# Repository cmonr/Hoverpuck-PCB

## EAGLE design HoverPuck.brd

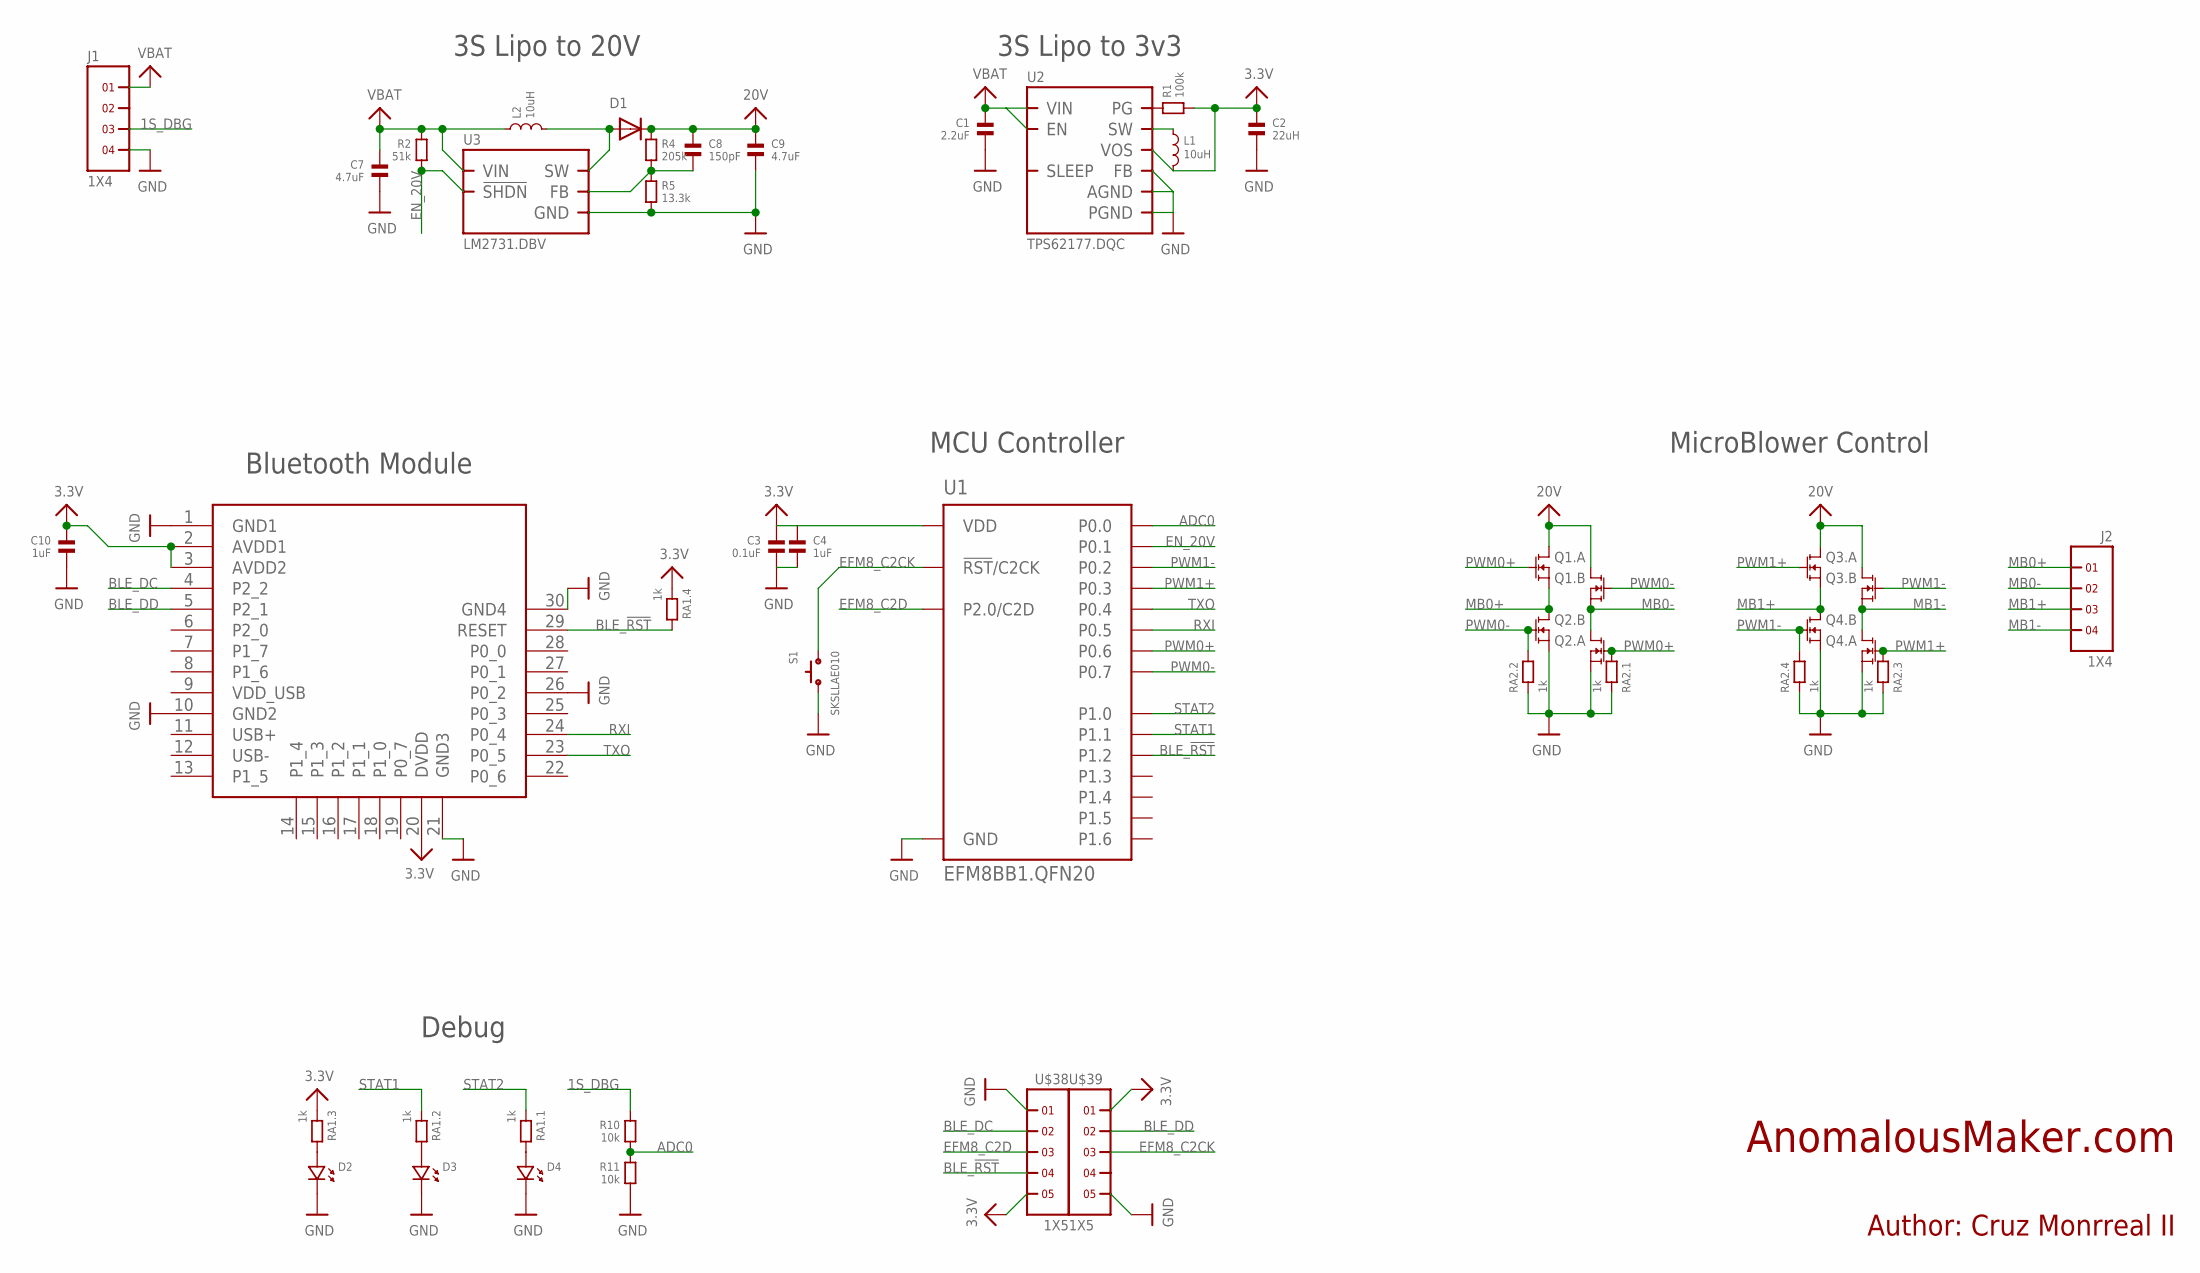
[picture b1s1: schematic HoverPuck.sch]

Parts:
C1: 2.2uF; 0603
C2: 22uH; 0805
C3: 0.1uF; 0603
C4, C10: 1uF; 0603
C7, C9: 4.7uF; 0805
C8: 150pF; 0603
D1: MBR0530T1G; SOD-123
D2, D3, D4: LED.0603; 0603.LED
J1, J2: 1X4
L1: 10uH; LPS4018
L2: 10uH; SRN6045
Q1, Q2, Q3, Q4: FDMA; MICROFET.2X2
R1: 100k; 0603
R2: 51k; 0603
R4: 205k; 0603
R5: 13.3k; 0603
R10, R11: 10k; 0603
RA1, RA2: 1k; 0603.4.C
S1: SKSLLAE010
U1: EFM8BB1.QFN20; QFN20
U2: TPS62177.DQC; DQC
U3: LM2731.DBV; DBV.5
U4: BLE112-A
U$38, U$39: 1X5

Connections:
1S_DBG: J1.3, R10.1
3.3V: C2.1, C3.1, C4.1, C10.1, L1.2, R1.2, RA1.5 (1), RA1.7 (1), U1.4 (VDD), U2.10 (VOS), U4.2 (AVDD1), U4.3 (AVDD2), U4.20 (DVDD), U$38.5, U$39.1
20V: C8.1, C9.1, D1.C, Q1.3 (D), Q1.6 (D), Q1.PAD@1 (D), Q1.PAD@2 (D), Q3.3 (D), Q3.6 (D), Q3.PAD@1 (D), Q3.PAD@2 (D), R4.1
ADC0: R10.2, R11.1, U1.2 (P0.0)
BLE_!RST: RA1.8 (2), U1.11 (P1.2), U4.29 (RESET), U$38.4
BLE_DC: U4.4 (P2_2), U$38.2
BLE_DD: U4.5 (P2_1), U$39.2
EFM8_C2CK: S1.1, U1.5 (!RST!/C2CK), U$39.3
EFM8_C2D: U1.6 (P2.0/C2D), U$38.3
EN_20V: R2.2, U1.1 (P0.1), U3.4 (!SHDN)
GND: C1.2, C2.2, C3.2, C4.2, C7.2, C9.2, C10.2, D2.P$2 (2), D3.P$2 (2), D4.P$2 (2), J1.4, Q2.1 (S), Q2.4 (S), Q4.1 (S), Q4.4 (S), R5.2, R11.2, RA2.1, RA2.3 (1), RA2.5 (1), RA2.7 (1), S1.2, U1.3 (GND), U1.12 (GND), U1.PAD (GND), U2.1 (PGND), U2.5 (FB), U2.6 (AGND), U2.PAD (PGND), U3.2 (GND), U4.1 (GND1), U4.10 (GND2), U4.21 (GND3), U4.26 (P0_2), U4.30 (GND4), U$38.1, U$39.5
MB0+: J2.1, Q1.1 (S), Q2.3 (D), Q2.PAD@2 (D)
MB0-: J2.2, Q1.4 (S), Q2.6 (D), Q2.PAD@1 (D)
MB1+: J2.3, Q3.1 (S), Q4.3 (D), Q4.PAD@2 (D)
MB1-: J2.4, Q3.4 (S), Q4.6 (D), Q4.PAD@1 (D)
unnamed: L1.1, U2.9 (SW)
unnamed: D2.P$1 (1), RA1.6 (2)
unnamed: D1.A, L2.2, U3.1 (SW)
unnamed: R1.1, U2.7 (PG)
unnamed: C8.2, R4.2, R5.1, U3.3 (FB)
unnamed: D3.P$1 (1), RA1.4 (2)
unnamed: D4.P$1 (1), RA1.2
PWM0+: Q1.2 (G), Q2.2 (G), RA2.2, U1.16 (P0.6)
PWM0-: Q1.5 (G), Q2.5 (G), RA2.4 (2), U1.15 (P0.7)
PWM1+: Q3.2 (G), Q4.2 (G), RA2.6 (2), U1.19 (P0.3)
PWM1-: Q3.5 (G), Q4.5 (G), RA2.8 (2), U1.20 (P0.2)
RXI: U1.17 (P0.5), U4.24 (P0_4)
STAT1: RA1.3 (1), U1.13 (P1.1)
STAT2: RA1.1, U1.14 (P1.0)
TXO: U1.18 (P0.4), U4.23 (P0_5)
VBAT: C1.1, C7.1, J1.1, L2.1, R2.1, U2.2 (VIN), U2.3 (EN), U3.5 (VIN)

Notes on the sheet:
3S Lipo to 3v3
MCU Controller
3S Lipo to 20V
Bluetooth Module
MicroBlower Control
Debug
Author: Cruz Monrreal II
AnomalousMaker.com

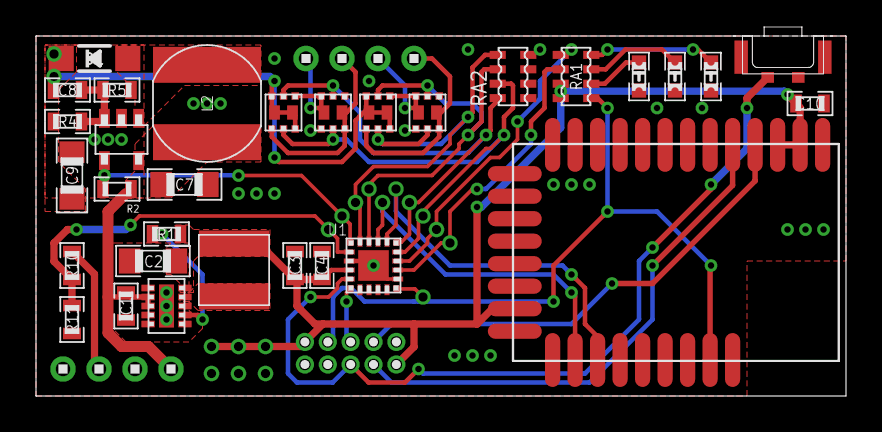
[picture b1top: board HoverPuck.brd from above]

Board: 2 copper layers, 45.0 x 20.0 mm, 35 parts (0 on the bottom side), 31 nets.

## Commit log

2015-03-18 Created HoverPuck project
2015-03-19 Schematic seems about done and layout of components looks promising Next step will be the actual routing
2015-03-19 A majority of routing completed. Switching regulators now completed. Minor MCU signals still needed, as well as labeling.
2015-03-19 Updated TODO list
    Added more references on what signals to breakout for BLE112
2015-03-19 Updated board file with more routing and placement
2015-03-19 Added single debugger connector
    Replaced 1k resistors with resistor array
2015-03-21 Completed v1 of HoverPuck PCB
2015-04-09 Started v2 of the HoverPuck. Changed driver circuit, and moving things around. New driver circuit still needs to be confirmed functional.
2015-04-10 Working on v1.1 Schematic almost complete, need to work on routing pins now. Decided to not be stingy and control the full H Brudge with two sets of PWMs instead of one. I have the pins, might as wel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
2015-04-12 HoverPuck v1.1 completed. Send to OSHPark and PCBWay

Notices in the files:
parts and their libraries:
microbuilder: This work is placed in the public domain, and may be freely used for commercial and non-commercial work with the following conditions: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
SparkFun-RF: Licensing: CC v3.0 Share-Alike You are welcome to use this library for commercial purposes.
